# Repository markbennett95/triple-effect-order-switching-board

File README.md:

# Triple Effect ORder Switching Board

A utility board for mounting foot switches and order switches for triple effect pedals in a 1590XX enclosure.

## v1.0.0-build
Has no LEDs. Features to "order" switches - one to swap the order of effect 1 and 2, the other to place effect 0 at the beginning or the end of the chain. Requires 2 8-connector ribbon cables, with connections as follows:

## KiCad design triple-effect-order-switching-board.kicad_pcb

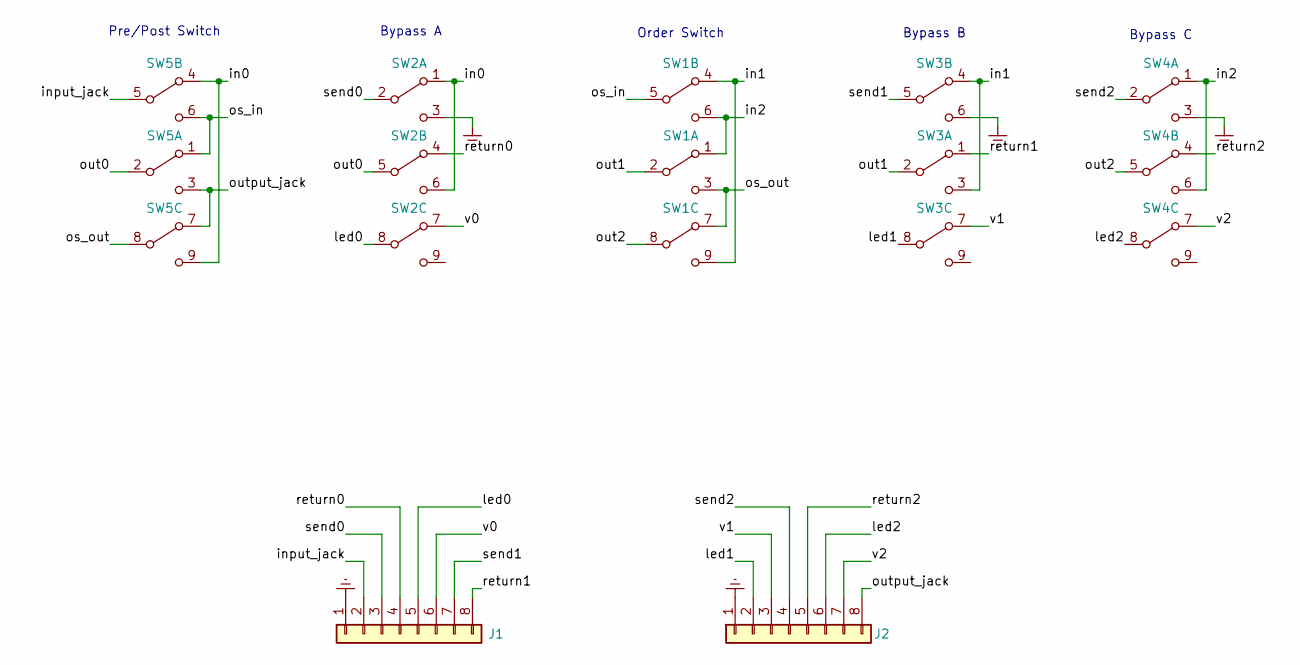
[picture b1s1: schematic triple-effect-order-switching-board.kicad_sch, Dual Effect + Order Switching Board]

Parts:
J1, J2: Conn_01x08; Pin_Header_Straight_1x08_Pitch2.54mm
SW1, SW5: SW_3PDT; SW_Toggle_3PDT_SolderLug
SW2, SW3, SW4: SW_3PDT; SW_Foot_3PDT

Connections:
/in0: SW2.1 (A), SW2.6 (C), SW5.4 (A), SW5.9 (C)
/in1: SW1.4 (A), SW1.9 (C), SW3.3 (C), SW3.4 (A)
/in2: SW1.1 (A), SW1.6 (C), SW4.1 (A), SW4.6 (C)
/input_jack: J1.2, SW5.5 (B)
/led0: J1.5, SW2.8 (B)
/led1: J2.2, SW3.8 (B)
/led2: J2.6, SW4.8 (B)
/os_in: SW1.5 (B), SW5.1 (A), SW5.6 (C)
/os_out: SW1.3 (C), SW1.7 (A), SW5.8 (B)
/out0: SW2.5 (B), SW5.2 (B)
/out1: SW1.2 (B), SW3.2 (B)
/out2: SW1.8 (B), SW4.5 (B)
/output_jack: J2.8, SW5.3 (C), SW5.7 (A)
/return0: J1.4, SW2.4 (A)
/return1: J1.8, SW3.1 (A)
/return2: J2.5, SW4.4 (A)
/send0: J1.3, SW2.2 (B)
/send1: J1.7, SW3.5 (B)
/send2: J2.4, SW4.2 (B)
/v0: J1.6, SW2.7 (A)
/v1: J2.3, SW3.7 (A)
/v2: J2.7, SW4.7 (A)
Earth: J1.1, J2.1, SW2.3 (C), SW3.6 (C), SW4.3 (C)

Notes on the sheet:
Pre/Post Switch
Bypass B
Order Switch
Bypass C
Bypass A

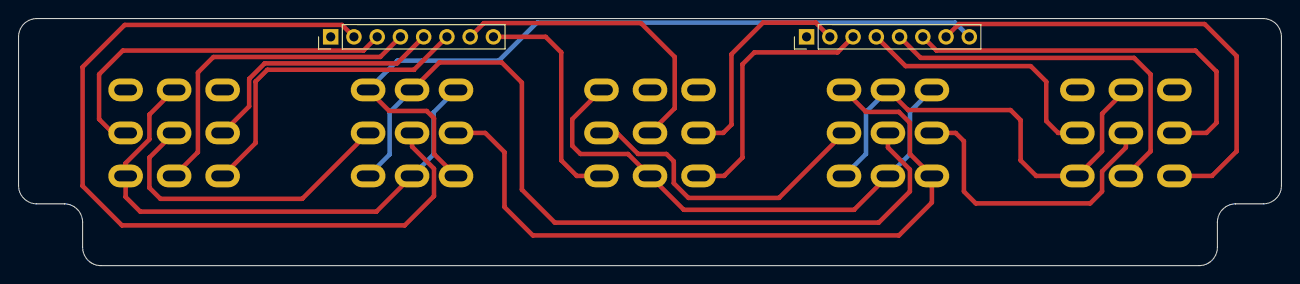
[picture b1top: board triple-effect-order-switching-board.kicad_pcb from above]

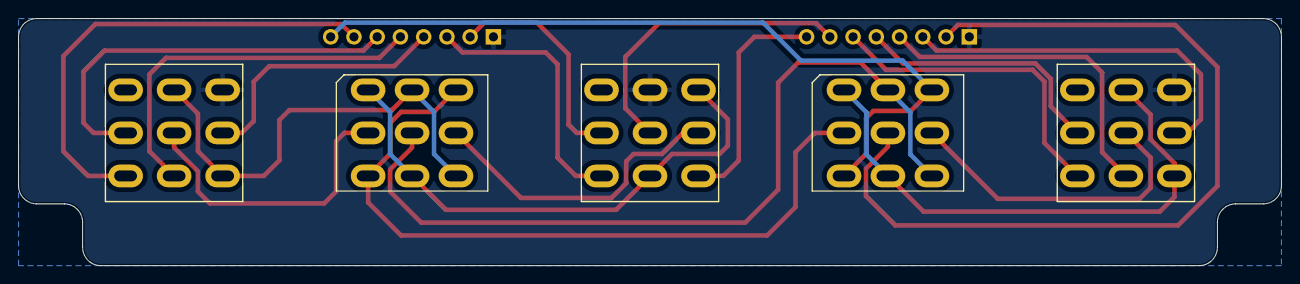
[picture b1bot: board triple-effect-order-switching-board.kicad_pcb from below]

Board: 2 copper layers, 138.0 x 27.0 mm, 7 parts (5 on the bottom side), 23 nets.

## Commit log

2026-02-19 renamed files
2026-03-18 finished board
